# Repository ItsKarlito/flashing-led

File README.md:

# flashing-led
Making PCB (printed circuit board) of a very popular electrical circuit that flashes an LED using a 555 timer IC.

[Demo video (.mp4 download link)](https://github.com/ItsKarlito/flashing-led/raw/master/media/demo.mp4)

**Circuit Schematic and PCB:**

**CAD Software:** 
[KiCad](https://www.kicad.org/)

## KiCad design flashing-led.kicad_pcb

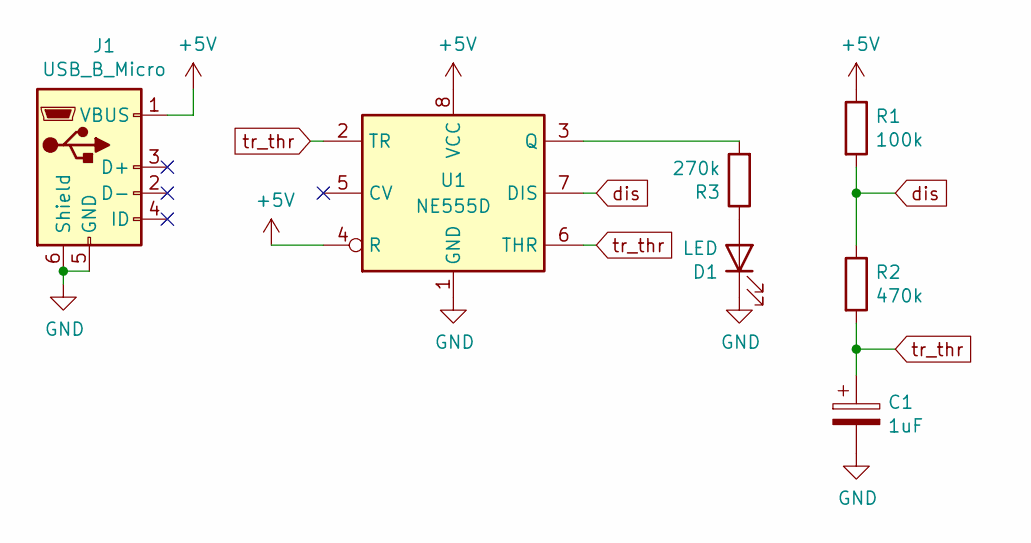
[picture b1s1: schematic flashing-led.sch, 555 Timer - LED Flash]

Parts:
C1: 1uF; CP_Elec_3x5.3
D1: LED; LED_0805_2012Metric
J1: USB_B_Micro; USB_Micro-B_Molex_47346-0001
R1: 100k; R_0805_2012Metric
R2: 470k; R_0805_2012Metric
R3: 270k; R_0805_2012Metric
U1: NE555D; SOIC-8_3.9x4.9mm_P1.27mm

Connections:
+5V: J1.1 (VBUS), R1.1, U1.4 (R), U1.8 (VCC)
GND: C1.2, D1.1 (K), J1.5 (GND), J1.6 (Shield), U1.1 (GND)
unnamed: D1.2 (A), R3.1
unnamed: R3.2, U1.3 (Q)
dis: R1.2, R2.1, U1.7 (DIS)
tr_thr: C1.1, R2.2, U1.2 (TR), U1.6 (THR)

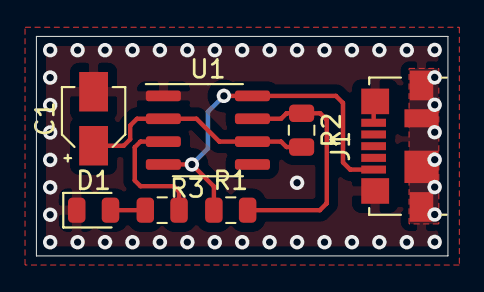
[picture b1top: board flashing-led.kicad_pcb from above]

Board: 2 copper layers, 22.9 x 12.2 mm, 7 parts (0 on the bottom side), 6 nets.

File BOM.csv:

Digikey,Reference, Quantity, Value,Description, Footprint
493-2129-2-ND,C1 ,1,1uF,Capacitor,Capacitor_SMD:CP_Elec_3x5.3
VAOL-S8SB4TR-ND,D1 ,1,LED,LED,LED_SMD:LED_0805_2012Metric
WM17141TR-ND,J1 ,1,USB_B_Micro,Female USB Micro B Connector,Connector_USB:USB_Micro-B_Molex_47346-0001
311-100KCRTR-ND,R1 ,1,100k,Resistor,Resistor_SMD:R_0805_2012Metric
311-470KCRTR-ND,R2 ,1,470k,Resistor,Resistor_SMD:R_0805_2012Metric
311-270KCRTR-ND,R3 ,1,270k,Resistor,Resistor_SMD:R_0805_2012Metric
296-16792-ND,U1 ,1,NE555D,IC,Package_SO:SOIC-8_3.9x4.9mm_P1.27mm

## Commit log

2020-01-19 Circuit schematic
2020-01-19 Assigned PCB footprints to schematic symbols
2020-01-19 Added schematic schreenshot
2020-01-19 PCB layout and traces
2020-01-19 Added screenshots
2020-04-05 added Vcc and GND pours
2020-04-05 repositioned silk screen component labels
2020-04-05 updated images
2020-04-05 added .gitignore and removed backup files
2020-04-14 Created and added LICENSE file.
2020-06-15 updated schematic and pcb
2020-06-15 generated gerber files
2020-06-15 updated .gitignore
2020-06-15 updated schematic image
2020-07-18 added image of physical pcb, updated README.md
2020-07-18 added BOM (bill of materials), added flashing-led.xml
2020-07-24 added demo video and image of soldered pcb
2020-07-24 removed duplicate image directory
2021-01-12 uploaded smaller image file for pcb_manufactured.png
